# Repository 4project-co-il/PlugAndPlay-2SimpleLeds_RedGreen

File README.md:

# PlugAndPlay: Module with 2 simple LEDs - Red and Green
This is the repository with the files for PlugAndPlay module with 2 simple LEDs: Red and Green.

The LED is connected to interrupt line #1 of the PnP connector.

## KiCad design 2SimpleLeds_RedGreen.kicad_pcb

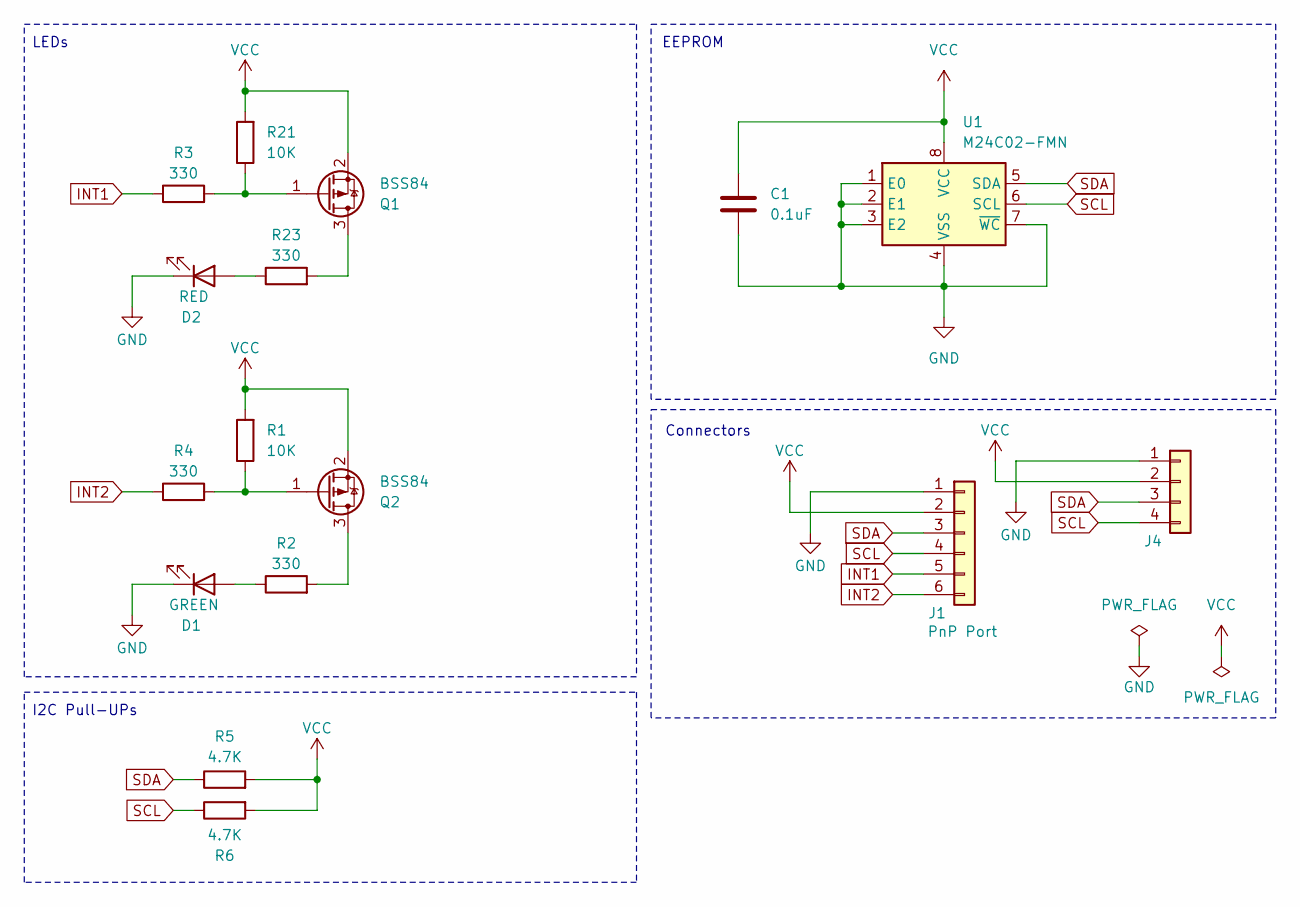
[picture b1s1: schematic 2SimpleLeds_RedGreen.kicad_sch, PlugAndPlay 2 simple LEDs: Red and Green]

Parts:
C1: 0.1uF; C_0603_1608Metric; MPN C14663
D1: GREEN; LED_0603_1608Metric; MPN C965804
D2: RED; LED_0603_1608Metric; MPN C965799
J1: JST_SH_SM06B-SRSS-TB_1x06-1MP_P1.00mm_Horizontal; MPN C7430448
J4: Conn_01x04; PogoPinsPads_1x04_P2.5mm
Q1, Q2: BSS84; SOT-23; MPN C114481
R1, R21: 10K; R_0603_1608Metric; MPN C25804
R2, R3, R4, R23: 330; R_0603_1608Metric; MPN C23138
R5, R6: 4.7K; R_0603_1608Metric; MPN C4190
U1: M24C02-FMN; SOIC-8_3.9x4.9mm_P1.27mm; MPN C114502

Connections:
GND: C1.2, D1.1 (K), D2.1 (K), J1.1, J4.1, U1.1 (E0), U1.2 (E1), U1.3 (E2), U1.4 (VSS), U1.7 (~WC)
INT1: J1.5, R3.1
INT2: J1.6, R4.1
unnamed: D1.2 (A), R2.1
unnamed: D2.2 (A), R23.1
unnamed: Q1.3 (D), R23.2
unnamed: Q1.1 (G), R3.2, R21.1
unnamed: Q2.3 (D), R2.2
unnamed: Q2.1 (G), R1.1, R4.2
SCL: J1.4, J4.4, R6.1, U1.6 (SCL)
SDA: J1.3, J4.3, R5.1, U1.5 (SDA)
VCC: C1.1, J1.2, J4.2, Q1.2 (S), Q2.2 (S), R1.2, R5.2, R6.2, R21.2, U1.8 (VCC)

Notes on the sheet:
EEPROM
LEDs
Connectors
I2C Pull-UPs

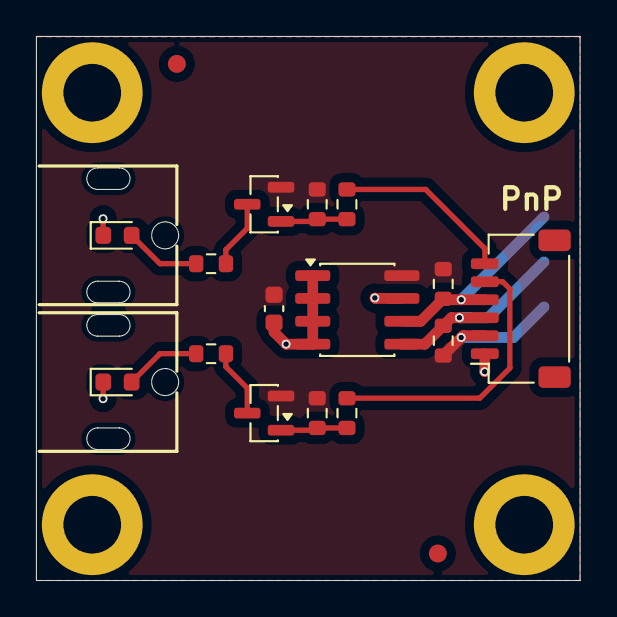
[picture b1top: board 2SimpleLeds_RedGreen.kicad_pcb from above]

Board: 2 copper layers, 30.2 x 30.2 mm, 16 parts (1 on the bottom side), 12 nets.
